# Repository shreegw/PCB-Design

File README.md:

# PCB-Design
PCB Design Projects using KiCad and Autodesk Fusion

## 1. Single Channel Relay [(Link)](https://github.com/shreegw/PCB-Design/tree/main/1_Channel_Relay)

## 2. Basic WeMos Mask [(Link)](https://github.com/shreegw/PCB-Design/blob/main/Wemos)

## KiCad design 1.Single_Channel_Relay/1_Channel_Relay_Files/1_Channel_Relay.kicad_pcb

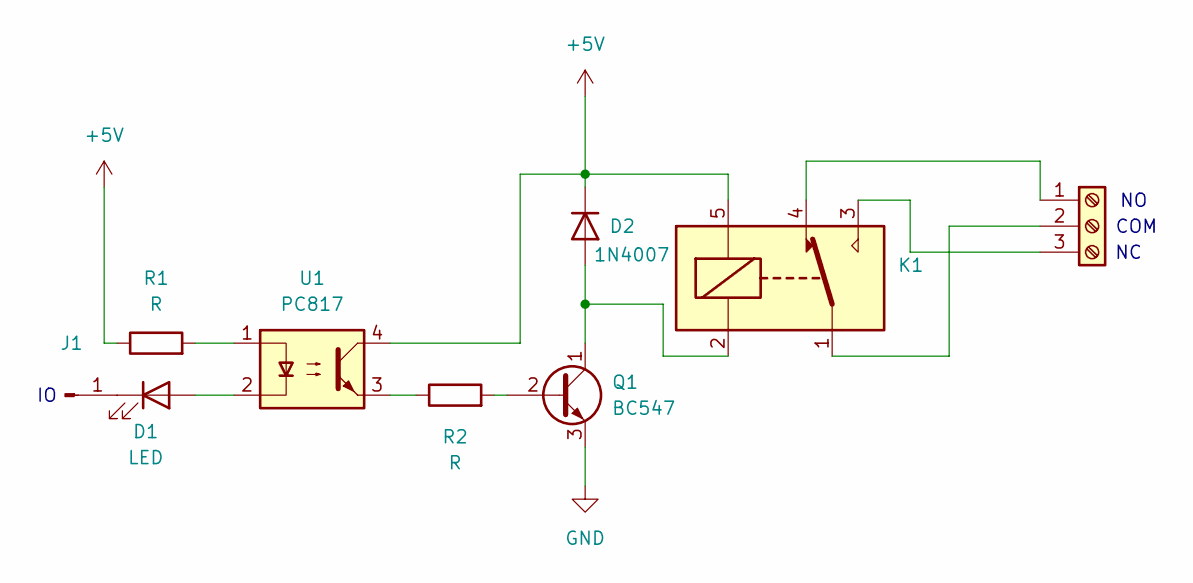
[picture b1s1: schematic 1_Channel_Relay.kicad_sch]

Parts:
D1: LED; LED_D1.8mm_W1.8mm_H2.4mm_Horizontal_O1.27mm_Z1.6mm
D2: 1N4007; D_DO-41_SOD81_P10.16mm_Horizontal
J1: Conn_01x01_Pin; PinHeader_1x01_P2.54mm_Vertical
J2: Screw_Terminal_01x03; TerminalBlock_RND_205-00002_1x03_P5.00mm_Horizontal
K1: SANYOU_SRD_Form_C; Relay_SPDT_SANYOU_SRD_Series_Form_C
Q1: BC547; TO-92_Inline
R1, R2: R; R_Axial_DIN0207_L6.3mm_D2.5mm_P7.62mm_Horizontal
U1: PC817; DIP-4_W7.62mm

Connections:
+5V: D2.1 (K), K1.5, R1.1, U1.4
GND: Q1.3 (E)
unnamed: D1.2 (A), U1.2
unnamed: D1.1 (K), J1.1
unnamed: D2.2 (A), K1.2, Q1.1 (C)
unnamed: J2.1, K1.4
unnamed: J2.2, K1.1
unnamed: J2.3, K1.3
unnamed: Q1.2 (B), R2.2
unnamed: R1.2, U1.1
unnamed: R2.1, U1.3

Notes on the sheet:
COM

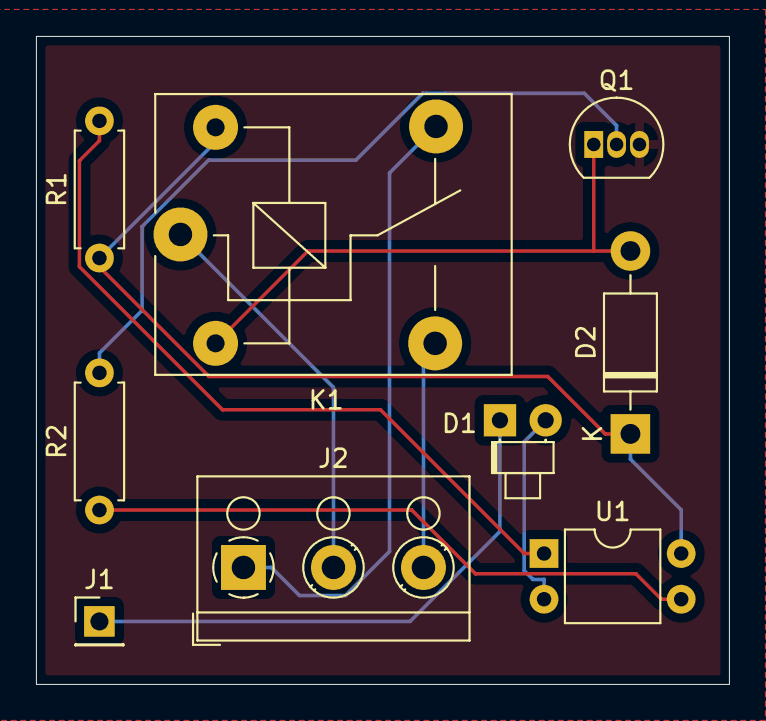
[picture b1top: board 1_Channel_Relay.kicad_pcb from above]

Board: 2 copper layers, 38.5 x 36.0 mm, 9 parts (0 on the bottom side), 10 nets.

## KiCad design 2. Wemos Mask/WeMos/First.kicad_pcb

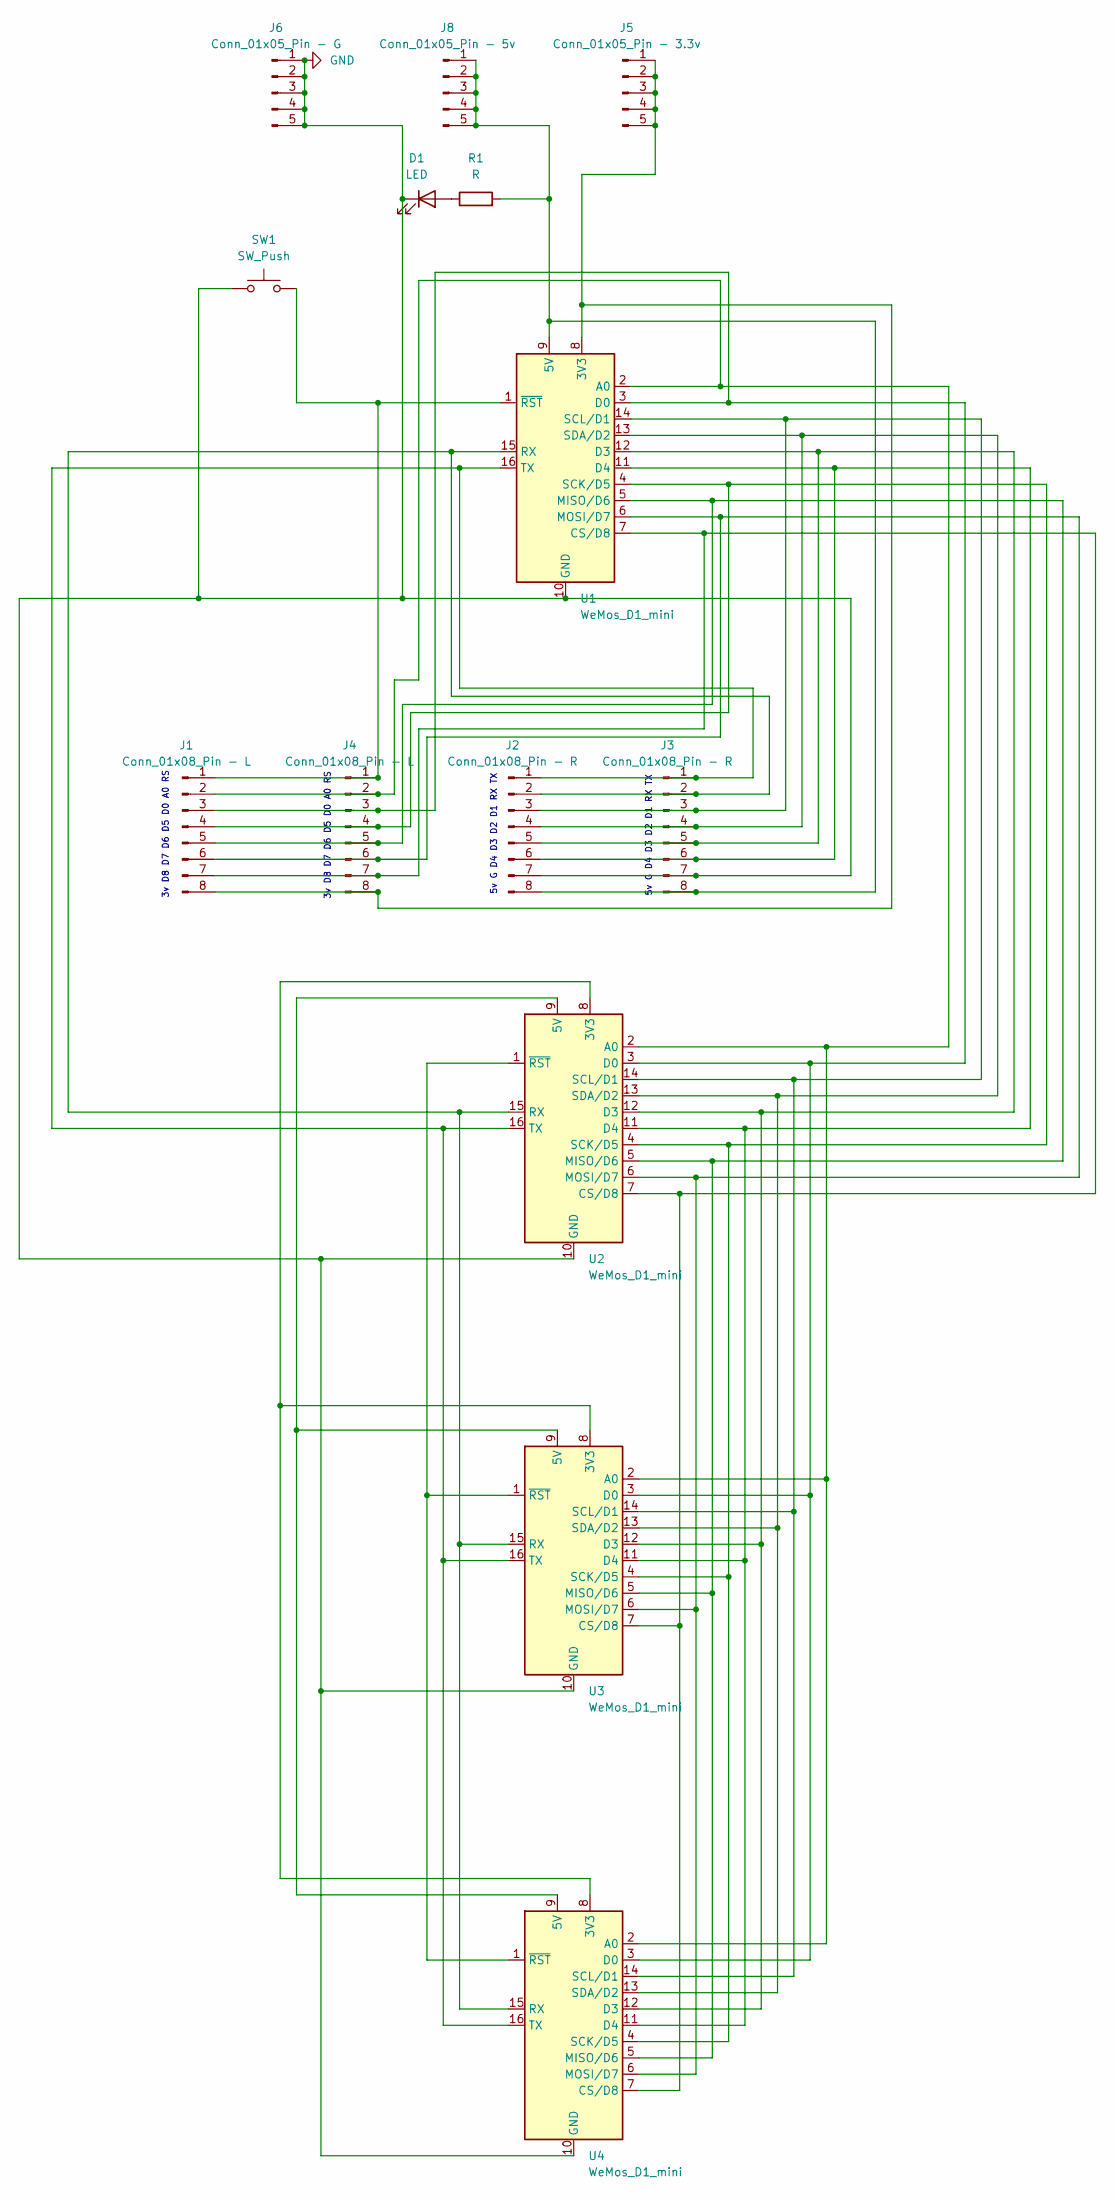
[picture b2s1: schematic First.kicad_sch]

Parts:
D1: LED; LED_D3.0mm
J1: Conn_01x08_Pin - L; PinHeader_1x08_P2.54mm_Vertical
J2: Conn_01x08_Pin - R; PinHeader_1x08_P2.54mm_Vertical
J3: Conn_01x08_Pin - R; TerminalBlock_RND_205-00018_1x08_P5.00mm_Horizontal
J4: Conn_01x08_Pin - L; TerminalBlock_RND_205-00018_1x08_P5.00mm_Horizontal
J5: Conn_01x05_Pin - 3.3v; PinSocket_1x05_P2.54mm_Vertical
J6: Conn_01x05_Pin - G; PinSocket_1x05_P2.54mm_Vertical
J8: Conn_01x05_Pin - 5v; PinSocket_1x05_P2.54mm_Vertical
R1: R; R_Axial_DIN0207_L6.3mm_D2.5mm_P7.62mm_Horizontal
SW1: SW_Push; SW_PUSH_6mm_H5mm
U1, U2, U3, U4: WeMos_D1_mini; WEMOS_D1_mini_light

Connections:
GND: D1.1 (K), J2.7, J3.7, J6.1, J6.2, J6.3, J6.4, J6.5, SW1.1, U1.10 (GND), U2.10 (GND), U3.10 (GND), U4.10 (GND)
unnamed: D1.2 (A), R1.1
unnamed: J1.1, J4.1, SW1.2, U1.1 (~RST)
unnamed: J1.2, J4.2, U1.2 (A0), U2.2 (A0), U3.2 (A0), U4.2 (A0)
unnamed: J1.3, J4.3, U1.3 (D0), U2.3 (D0), U3.3 (D0), U4.3 (D0)
unnamed: J1.4, J4.4, U1.4 (SCK/D5), U2.4 (SCK/D5), U3.4 (SCK/D5), U4.4 (SCK/D5)
unnamed: J1.5, J4.5, U1.5 (MISO/D6), U2.5 (MISO/D6), U3.5 (MISO/D6), U4.5 (MISO/D6)
unnamed: J1.6, J4.6, U1.6 (MOSI/D7), U2.6 (MOSI/D7), U3.6 (MOSI/D7), U4.6 (MOSI/D7)
unnamed: J1.7, J4.7, U1.7 (CS/D8), U2.7 (CS/D8), U3.7 (CS/D8), U4.7 (CS/D8)
unnamed: J1.8, J4.8, J5.1, J5.2, J5.3, J5.4, J5.5, U1.8 (3V3)
unnamed: J2.1, J3.1, U1.16 (TX), U2.16 (TX), U3.16 (TX), U4.16 (TX)
unnamed: J2.2, J3.2, U1.15 (RX), U2.15 (RX), U3.15 (RX), U4.15 (RX)
unnamed: J2.3, J3.3, U1.14 (SCL/D1), U2.14 (SCL/D1), U3.14 (SCL/D1), U4.14 (SCL/D1)
unnamed: J2.4, J3.4, U1.13 (SDA/D2), U2.13 (SDA/D2), U3.13 (SDA/D2), U4.13 (SDA/D2)
unnamed: J2.5, J3.5, U1.12 (D3), U2.12 (D3), U3.12 (D3), U4.12 (D3)
unnamed: J2.6, J3.6, U1.11 (D4), U2.11 (D4), U3.11 (D4), U4.11 (D4)
unnamed: J2.8, J3.8, J8.1, J8.2, J8.3, J8.4, J8.5, R1.2, U1.9 (5V)
unnamed: U2.8 (3V3), U3.8 (3V3), U4.8 (3V3)
unnamed: U2.9 (5V), U3.9 (5V), U4.9 (5V)
unnamed: U2.1 (~RST), U3.1 (~RST), U4.1 (~RST)

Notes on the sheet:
5v G D4 D3 D2 D1 RX TX
3v D8 D7 D6 D5 D0 A0 RS

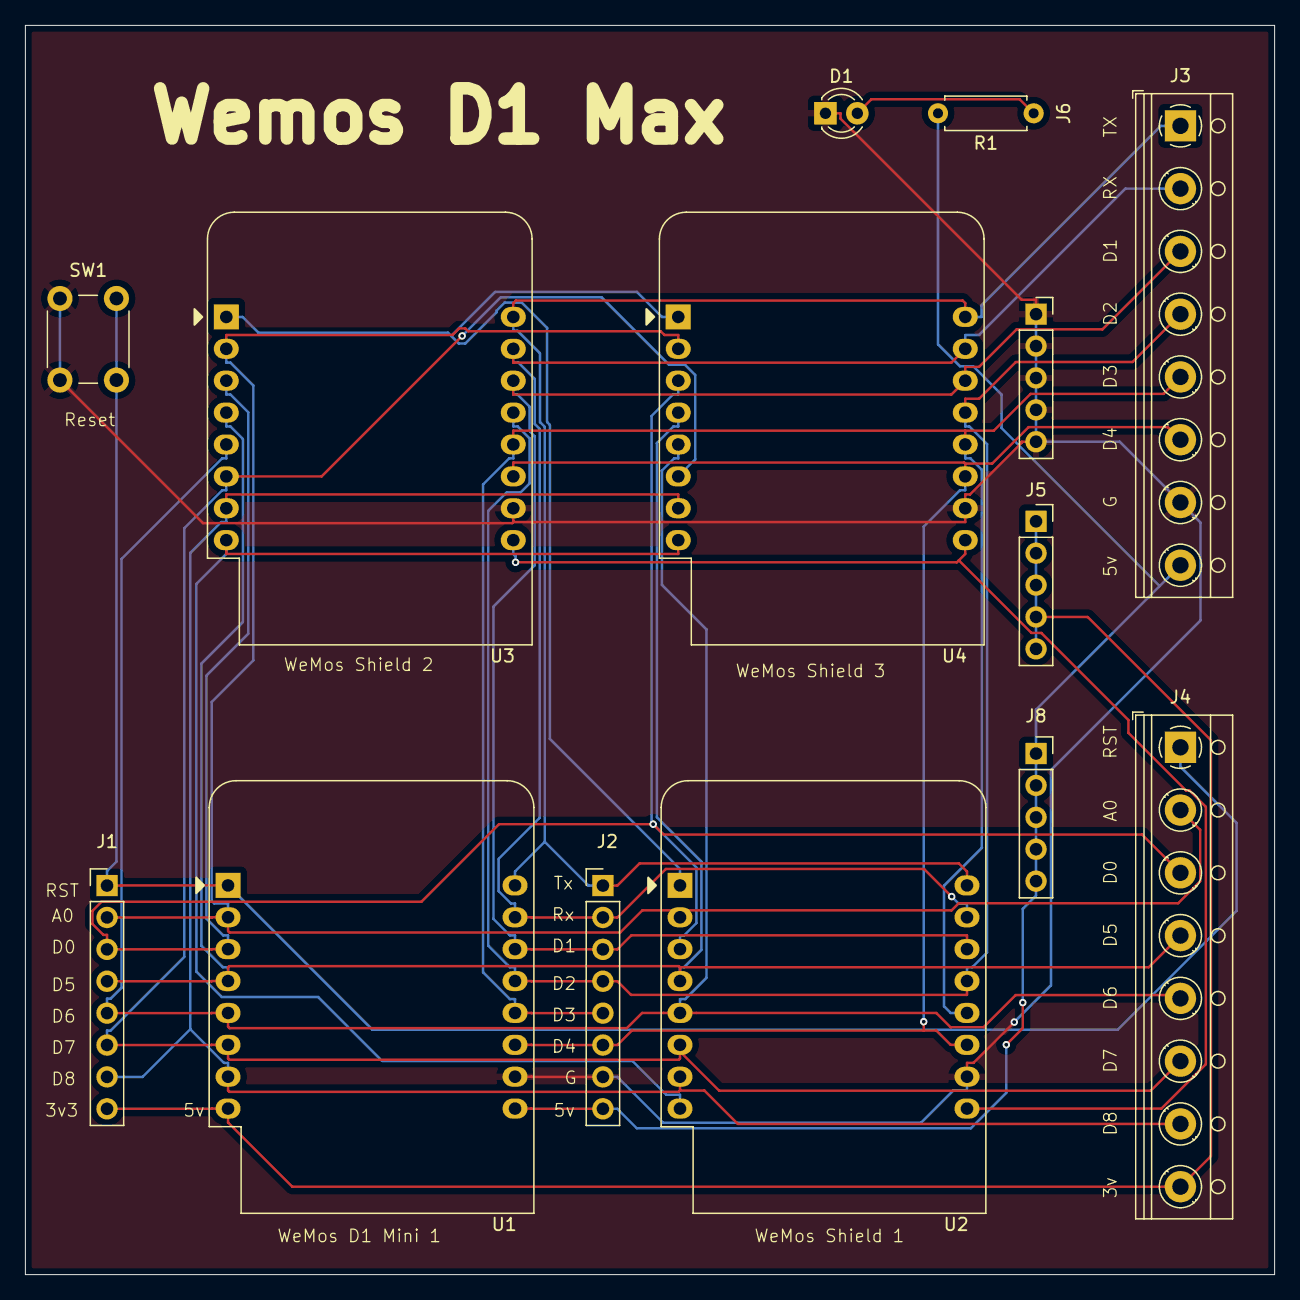
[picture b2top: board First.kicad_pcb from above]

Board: 2 copper layers, 99.5 x 99.5 mm, 14 parts (0 on the bottom side), 20 nets.

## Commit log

2024-07-30 Create WemosPCB Files
2024-08-06 Create Files
2024-12-23 Edit File Names
